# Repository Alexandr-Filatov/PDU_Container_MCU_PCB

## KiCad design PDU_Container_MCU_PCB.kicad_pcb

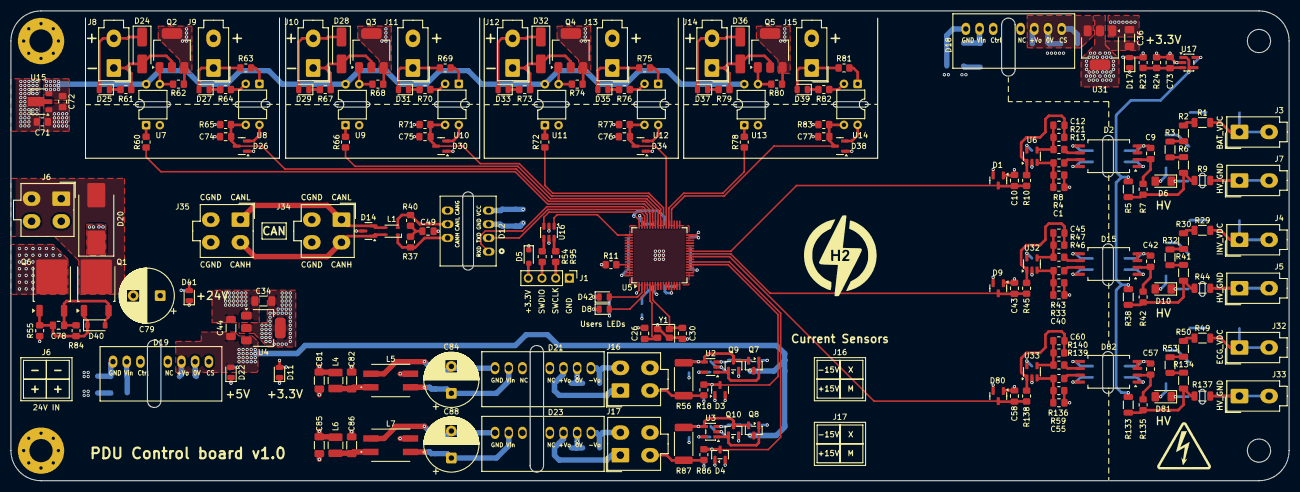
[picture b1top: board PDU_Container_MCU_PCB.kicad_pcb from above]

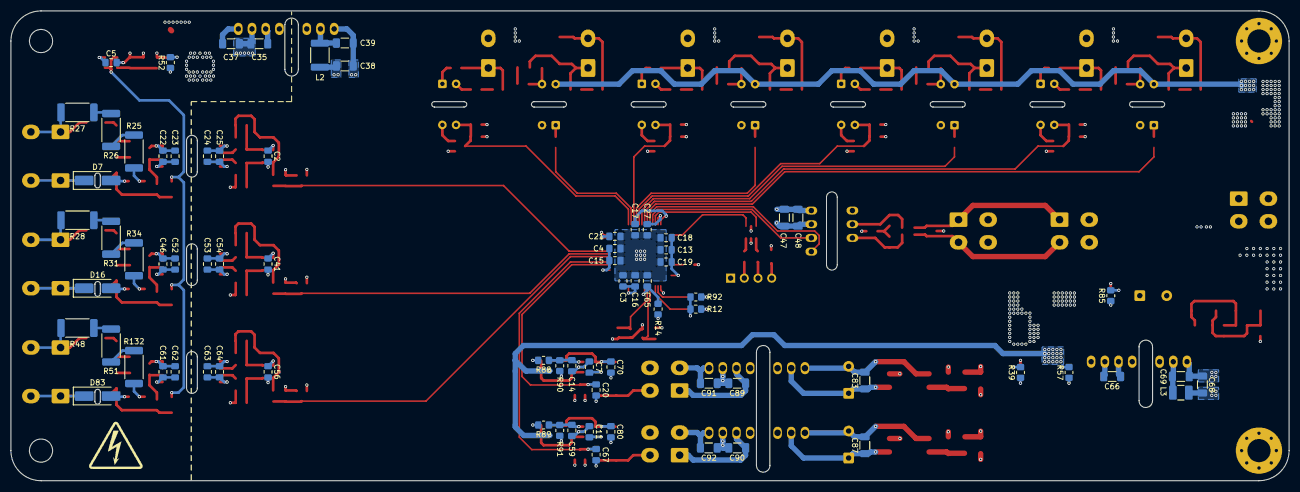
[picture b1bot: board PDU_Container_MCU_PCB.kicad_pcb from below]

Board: 4 copper layers, 237.2 x 87.2 mm, 283 parts (75 on the bottom side), 150 nets.

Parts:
C1, C9, C12, C40, C42, C45, C55, C57, C60: 56p; C_0805_2012Metric_Pad1.18x1.45mm_HandSolder
C2, C3, C4, C5, C7, C11, C13, C14, C15, C17, C18, C23, C25, C41, C52, C54, C56, C59, C62, C64, C65, C73, C78: 100n; C_0805_2012Metric_Pad1.18x1.45mm_HandSolder
C10, C43, C58: 220n; C_0805_2012Metric_Pad1.18x1.45mm_HandSolder
C16: 4.7u; C_0805_2012Metric_Pad1.18x1.45mm_HandSolder
C19, C74, C75, C76, C77: 1u; C_0805_2012Metric_Pad1.18x1.45mm_HandSolder
C20, C49, C67: 10n; C_0805_2012Metric_Pad1.18x1.45mm_HandSolder
C21, C22, C24, C27, C46, C53, C61, C63: 2.2u; C_0805_2012Metric_Pad1.18x1.45mm_HandSolder
C26, C30: 12p; C_0805_2012Metric_Pad1.18x1.45mm_HandSolder
C34, C35, C36, C37, C38, C44, C47, C66, C81, C82, C83, C85, C86, C87, C89, C90, C91, C92: 10u; C_1206_3216Metric_Pad1.33x1.80mm_HandSolder
C39: 1u; C_1206_3216Metric_Pad1.33x1.80mm_HandSolder
C48: 100n; C_1206_3216Metric_Pad1.33x1.80mm_HandSolder
C68, C69: 4.7u; C_1206_3216Metric_Pad1.33x1.80mm_HandSolder
C70, C71, C72, C80: 10u; C_0805_2012Metric_Pad1.18x1.45mm_HandSolder
C79, C84, C88: 330u; CP_Radial_D10.0mm_P5.00mm
D1, D3, D4, D9, D14, D26, D30, D34, D38, D80: SOT-23
D2, D15, D82: SOIC-8_7.5x5.85mm_P1.27mm
D5: D_SOD-323_HandSoldering
D6, D10, D81: LED_1206_3216Metric_Pad1.42x1.75mm_HandSolder
D7, D16, D24, D28, D32, D36, D83: D_SMA_Handsoldering
D8, D11, D17, D22, D25, D27, D29, D31, D33, D35, D37, D39, D41, D42: LED_0805_2012Metric
D12: TD5(3)01MCANFD
D13: Logo; Logo_Company_1
D18, D19: WRB_S-3WR2
D20: D_SMC_Handsoldering
D21, D23: UWE_S-3WR3
D40: D_SOD-123
H1, H2: MountingHole_Pad; MountingHole_4.3mm_M4_Pad_Via
H3, H4: MountingHole; MountingHole_4.3mm_M4
J1: PinHeader_1x04_P2.54mm_Vertical
J3, J4, J5, J7, J8, J9, J10, J11, J12, J13, J14, J15, J32, J33: Mini-Fit_01x02_Vertical
J6, J16, J17, J34, J35: Molex_Mini-Fit_Jr_5566-04A_2x02_P4.20mm_Vertical
L1: L_CommonModeChoke_TDK_ACM2520-2P
L2: 4.7u; L_1812_4532Metric_Pad1.30x3.40mm_HandSolder
L3: 6.8u; L_1210_3225Metric_Pad1.42x2.65mm_HandSolder
L4, L6: 4.7u; L_1210_3225Metric_Pad1.42x2.65mm_HandSolder
L5, L7: 470u; B82790S0513N201
Q1, Q6: TO-252-2
Q2, Q3, Q4, Q5: SOT-223
Q7, Q8, Q9, Q10: SOT-23
R1, R2, R3, R6, R29, R30, R32, R41, R49, R50, R53, R134: 2M; R_1206_3216Metric
R4, R8, R12, R13, R18, R21, R33, R39, R43, R46, R47, R52, R57, R59, R86, R92, R136, R139, R140: 1k; R_0805_2012Metric_Pad1.20x1.40mm_HandSolder
R5, R9, R38, R44, R133, R137: 8k; R_1206_3216Metric
R7, R10, R42, R45, R135, R138: 120; R_0805_2012Metric_Pad1.20x1.40mm_HandSolder
R11, R14, R24, R62, R65, R68, R71, R74, R77, R80, R83, R88, R89, R90, R91: 10k; R_0805_2012Metric_Pad1.20x1.40mm_HandSolder
R23: 23.2k; R_0805_2012Metric_Pad1.20x1.40mm_HandSolder
R25, R26, R27, R28, R31, R34, R48, R51, R132: 150k; R_2512_6332Metric_Pad1.40x3.35mm_HandSolder
R37, R40: 59; R_0805_2012Metric_Pad1.20x1.40mm_HandSolder
R54, R95: 20; R_0805_2012Metric_Pad1.20x1.40mm_HandSolder
R55: 100k; R_0805_2012Metric_Pad1.20x1.40mm_HandSolder
R56, R87: 14.3; R_2512_6332Metric_Pad1.40x3.35mm_HandSolder
R60, R66, R72, R78: 330; R_0805_2012Metric_Pad1.20x1.40mm_HandSolder
R61, R64, R67, R70, R73, R76, R79, R82: 8.2k; R_0805_2012Metric_Pad1.20x1.40mm_HandSolder
R63, R69, R75, R81: 3.3k; R_0805_2012Metric_Pad1.20x1.40mm_HandSolder
R84: 470k; R_0805_2012Metric_Pad1.20x1.40mm_HandSolder
R85: 4.7k; R_0805_2012Metric_Pad1.20x1.40mm_HandSolder
U2, U3, U6, U17, U32, U33: SOT-23-5
U4, U31: SOT-223-3_TabPin2
U5: LQFP-64_10x10mm_P0.5mm
U7, U8, U9, U10, U11, U12, U13, U14: DIP-4_W7.62mm
U15: SOT-89-3
U16: SOT-23-6
Y1: 16M; Crystal_SMD_SeikoEpson_FA238-4Pin_3.2x2.5mm

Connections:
+1V0: R5.2, R38.2, R133.2, U17.1, U17.4 (-)
+3.3V: C2.1, C3.1, C4.1, C7.1, C11.1, C13.1, C15.1, C16.1, C17.1, C18.1, C19.1, C24.2, C25.1, C34.2, C41.1, C47.1, C48.1, C53.2, C54.1, C56.1, C63.2, C64.1, D1.2 (K), D2.8 (VDD2), D3.2 (K), D4.2 (K), D5.1 (K), D9.2 (K), D11.2 (A), D12.4 (VCC), D15.8 (VDD2), D26.2 (K), D30.2 (K), D34.2 (K), D38.2 (K), D80.2 (K), D82.8 (VDD2), R14.1, R88.1, R89.1, U2.5 (V+), U3.5 (V+), U4.2 (VO), U5.1 (VBAT), U5.13 (VDDA), U5.19 (VDD), U5.32 (VDD), U5.48 (VDD), U5.64 (VDD), U6.5 (V+), U8.4, U10.4, U12.4, U14.4, U16.5 (VBUS), U32.5 (V+), U33.5 (V+)
+3.3VP: C5.1, C22.2, C23.1, C36.2, C46.2, C52.1, C61.2, C62.1, D2.1 (VDD1), D15.1 (VDD1), D17.2 (A), D82.1 (VDD1), R23.1, U17.5 (V+), U31.2 (VO)
+5V: C44.2, C66.1, D19.6 (+Vo), D22.2 (A), Q7.3 (C), Q8.3 (C), U4.3 (VI)
+5VD: C72.1, U7.4, U9.4, U11.4, U13.4, U15.3 (VOUT)
+24V: C38.1, C68.1, C71.1, C79.1, C81.1, C85.1, D20.1 (A1), D24.1 (K), D25.2 (A), D28.1 (K), D29.2 (A), D32.1 (K), D33.2 (A), D36.1 (K), D37.2 (A), D41.2 (A), J6.2, J6.4, J8.2, J9.2, J10.2, J11.2, J12.2, J13.2, J14.2, J15.2, L2.1, L3.1, L4.1, L6.1, R55.2, U15.2 (VIN)
-24V_IN: D20.2 (A2), J6.1, J6.3, Q1.2 (D)
/CANH: D14.1 (K), J34.2, J35.2, L1.4
/CANL: D14.2 (K), J34.1, J35.1, L1.3
/CAN_RXD_MCU: D12.1 (RXD), U5.44 (PA11)
/CAN_TXD_MCU: D12.2 (TXD), U5.45 (PA12)
/Current_1_measure: C20.1, D3.3 (common), R18.2, U5.21 (PA5)
/Current_2_measure: C67.1, D4.3 (common), R86.2, U5.22 (PA6)
/Current_measure_1/+15V: C89.1, D21.6 (+Vo), J16.1
/Current_measure_1/-15V: C91.2, D21.8 (-Vo), J16.2
/Current_measure_1/M: J16.3, R18.1, R56.2
/Current_measure_2/+15V: C90.1, D23.6 (+Vo), J17.1
/Current_measure_2/-15V: C92.2, D23.8 (-Vo), J17.2
/Current_measure_2/M: J17.3, R86.1, R87.2
/Relay_Control_1: R60.1, U5.43 (PA10)
/Relay_Control_2: R66.1, U5.41 (PA8)
/Relay_Control_3: R72.1, U5.39 (PC8)
/Relay_Control_4: R78.1, U5.37 (PC6)
/Relay_FeedBack_1: C74.1, D26.3 (common), R65.1, U5.42 (PA9), U8.3
/Relay_FeedBack_2: C75.1, D30.3 (common), R71.1, U5.40 (PC9), U10.3
/Relay_FeedBack_3: C76.1, D34.3 (common), R77.1, U5.38 (PC7), U12.3
/Relay_FeedBack_4: C77.1, D38.3 (common), R83.1, U5.36 (PB15), U14.3
/SWCLK: U5.49 (PA14), U16.1 (I/O1)
/SWDIO: U5.46 (PA13), U16.3 (I/O2)
/VDC_1_measure: C10.1, D1.3 (common), R10.2, U5.26 (PB0)
/VDC_2_measure: C43.1, D9.3 (common), R45.2, U5.25 (PC5)
/VDC_3_measure: C58.1, D80.3 (common), R138.2, U5.24 (PC4)
BOOT0: R11.2, U5.60 (BOOT0)
GND: C1.1, C2.2, C3.2, C4.2, C7.2, C10.2, C11.2, C13.2, C14.1, C15.2, C16.2, C17.2, C18.2, C19.2, C20.2, C21.2, C24.1, C25.2, C26.1, C27.2, C30.2, C34.1, C40.1, C41.2, C43.2, C44.1, C47.2, C48.2, C53.1, C54.2, C55.1, C56.2, C58.2, C59.1, C63.1, C64.2, C65.1, C66.2, C67.2, C70.2, C74.2, C75.2, C76.2, C77.2, C80.2, C89.2, C90.2, C91.1, C92.1, D1.1 (A), D2.5 (GND2), D3.1 (A), D4.1 (A), D9.1 (A), D12.3 (GND), D15.5 (GND2), D19.7 (0V), D21.7 (0V), D23.7 (0V), D26.1 (A), D30.1 (A), D34.1 (A), D38.1 (A), D80.1 (A), D82.5 (GND2), J1.1, Q9.2 (E), Q10.2 (E), R4.1, R11.1, R12.2, R33.1, R39.2, R57.2, R59.1, R65.2, R71.2, R77.2, R83.2, R90.1, R91.1, R92.2, U2.2 (V-), U3.2 (V-), U4.1 (GND), U5.12 (VSSA), U5.18 (VSS), U5.63 (VSS), U6.2 (V-), U7.2, U9.2, U11.2, U13.2, U16.2 (GND), U32.2 (V-), U33.2 (V-), Y1.2, Y1.4
GNDD: C38.2, C39.2, C68.2, C69.2, C71.2, C72.2, C79.2, C81.2, C82.2, C85.2, C86.2, D18.1 (GND), D19.1 (GND), H1.1 (1_1), H2.1 (1_1), L5.3, L7.3, Q2.3 (S), Q2.4 (S), Q3.3 (S), Q3.4 (S), Q4.3 (S), Q4.4 (S), Q5.3 (S), Q5.4 (S), Q6.2 (D), R62.1, R64.2, R68.1, R70.2, R74.1, R76.2, R80.1, R82.2, R85.2, U8.2, U10.2, U12.2, U14.2, U15.1 (GND)
GNDPWR: C5.2, C9.2, C22.1, C23.2, C35.1, C36.1, C37.1, C42.2, C46.1, C52.2, C57.2, C61.1, C62.2, C73.1, D2.3 (SHTDN), D2.4 (GND1), D7.1 (K), D15.3 (SHTDN), D15.4 (GND1), D16.1 (K), D18.7 (0V), D82.3 (SHTDN), D82.4 (GND1), D83.1 (K), J5.1, J5.2, J7.1, J7.2, J33.1, J33.2, R9.1, R24.2, R44.1, R52.2, R137.1, U17.2 (V-), U31.1 (GND)
GND_CAN: C49.2, D12.5 (CANG), D14.3 (A), J34.3, J34.4, J35.3, J35.4
NRST: C65.2, R14.2, U5.7 (NRST)
unnamed: C12.2, R10.1, R21.2, U6.1
unnamed: C45.2, R45.1, R47.2, U32.1
unnamed: C49.1, R37.1, R40.2
unnamed: C60.2, R138.1, R140.2, U33.1
unnamed: C82.1, L4.2, L5.1
unnamed: C86.1, L6.2, L7.1
unnamed: D2.6 (OUTN), R13.1
unnamed: D2.7 (OUTP), R8.1
unnamed: C9.1, D2.2 (VIN), R7.1
unnamed: D5.2 (A), J1.4
unnamed: D6.2 (A), R25.2
unnamed: D6.1 (K), D7.2 (A)
unnamed: D8.2 (A), U5.3 (PC14)
unnamed: D8.1 (K), R12.1
unnamed: D10.2 (A), R34.2
unnamed: D10.1 (K), D16.2 (A)
unnamed: D11.1 (K), R39.1
unnamed: D12.7 (CANH), L1.1, R37.2
unnamed: D12.6 (CANL), L1.2, R40.1
unnamed: D15.6 (OUTN), R46.1
unnamed: D15.7 (OUTP), R43.1
unnamed: C42.1, D15.2 (VIN), R42.1
unnamed: D17.1 (K), R52.1
unnamed: C35.2, D18.6 (+Vo), U31.3 (VI)
unnamed: C37.2, D18.8 (CS)
unnamed: C39.1, D18.2 (Vin), L2.2
unnamed: C69.1, D19.2 (Vin), L3.2
unnamed: C83.2, C84.2, D21.1 (GND), L5.4
unnamed: C83.1, C84.1, D21.2 (Vin), L5.2
unnamed: D22.1 (K), R57.1
unnamed: C87.2, C88.2, D23.1 (GND), L7.4
unnamed: C87.1, C88.1, D23.2 (Vin), L7.2
unnamed: D24.2 (A), J8.1, Q2.2 (D), R61.2
unnamed: D25.1 (K), R61.1
unnamed: D27.2 (A), J9.1, R63.2
unnamed: D27.1 (K), R64.1
unnamed: D28.2 (A), J10.1, Q3.2 (D), R67.2
unnamed: D29.1 (K), R67.1
unnamed: D31.2 (A), J11.1, R69.2
unnamed: D31.1 (K), R70.1
unnamed: D32.2 (A), J12.1, Q4.2 (D), R73.2
unnamed: D33.1 (K), R73.1
unnamed: D35.2 (A), J13.1, R75.2
unnamed: D35.1 (K), R76.1
unnamed: D36.2 (A), J14.1, Q5.2 (D), R79.2
unnamed: D37.1 (K), R79.1
unnamed: D39.2 (A), J15.1, R81.2
unnamed: D39.1 (K), R82.1
unnamed: C78.2, D40.2 (A), Q1.3 (S), Q6.3 (S), R84.2
unnamed: C78.1, D40.1 (K), Q1.1 (G), Q6.1 (G), R55.1, R84.1
unnamed: D41.1 (K), R85.1
unnamed: D42.2 (A), U5.2 (PC13)
unnamed: D42.1 (K), R92.1
unnamed: D81.2 (A), R132.2
unnamed: D81.1 (K), D83.2 (A)
unnamed: D82.6 (OUTN), R139.1
unnamed: D82.7 (OUTP), R136.1
unnamed: C57.1, D82.2 (VIN), R135.1
unnamed: J1.2, R95.2
unnamed: J1.3, R54.2
unnamed: J3.1, J3.2, R1.2, R27.1
unnamed: J4.1, J4.2, R28.1, R29.2
unnamed: J32.1, J32.2, R48.1, R49.2
unnamed: Q2.1 (G), R62.2, U7.3
unnamed: Q3.1 (G), R68.2, U9.3
unnamed: Q4.1 (G), R74.2, U11.3
unnamed: Q5.1 (G), R80.2, U13.3
unnamed: Q7.1 (B), Q9.1 (B), U2.1
unnamed: C70.1, Q7.2 (E), Q9.3 (C), R56.1, U2.4 (-)
unnamed: Q8.1 (B), Q10.1 (B), U3.1
unnamed: C80.1, Q8.2 (E), Q10.3 (C), R87.1, U3.4 (-)
unnamed: R1.1, R2.2
unnamed: R2.1, R3.2
unnamed: R3.1, R6.2
unnamed: R5.1, R6.1, R7.2, R9.2
unnamed: R25.1, R26.2
unnamed: R26.1, R27.2
unnamed: R28.2, R31.1
unnamed: R29.1, R30.2
unnamed: R30.1, R32.2
unnamed: R31.2, R34.1
unnamed: R32.1, R41.2
unnamed: R38.1, R41.1, R42.2, R44.2
unnamed: R48.2, R51.1
unnamed: R49.1, R50.2
unnamed: R50.1, R53.2
unnamed: R54.1, U16.4 (I/O2)
unnamed: R60.2, U7.1
unnamed: R63.1, U8.1
unnamed: R66.2, U9.1
unnamed: R69.1, U10.1
unnamed: R72.2, U11.1
unnamed: R75.1, U12.1
unnamed: R78.2, U13.1
unnamed: R81.1, U14.1
unnamed: R95.1, U16.6 (I/O1)
unnamed: R51.2, R132.1
unnamed: R133.1, R134.1, R135.2, R137.2
unnamed: R53.1, R134.2
unnamed: C14.2, R88.2, R90.2, U2.3 (+)
unnamed: C59.2, R89.2, R91.2, U3.3 (+)
unnamed: C26.2, U5.5 (PH0), Y1.3
unnamed: C30.1, U5.6 (PH1), Y1.1
unnamed: C21.1, U5.31 (VCAP_1)
unnamed: C27.1, U5.47 (VCAP_2)
unnamed: C1.2, R4.2, R8.2, U6.3 (+)
unnamed: C12.1, R13.2, R21.1, U6.4 (-)
unnamed: C73.2, R23.2, R24.1, U17.3 (+)
unnamed: C40.2, R33.2, R43.2, U32.3 (+)
unnamed: C45.1, R46.2, R47.1, U32.4 (-)
unnamed: C55.2, R59.2, R136.2, U33.3 (+)
unnamed: C60.1, R139.2, R140.1, U33.4 (-)

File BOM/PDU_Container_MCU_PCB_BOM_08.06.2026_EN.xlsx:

Reference | Value | Product Name | Replacement | Package | Description | Quantity | DNP
C23, C25, C52, C54, C62, C64 | 0.1u |  |  | SMD 0805 |  | 6
C48 | 0.1u |  |  | SMD 1206 |  | 1
C10, C43, C58 | 0.27u |  |  | SMD 0805 |  | 3
C2, C3, C5, C7, C11, C14, C16, C17, C18, C19, C27, C28, C29, C32, C33, C41, C56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 | 100n |  |  | SMD 0805 |  | 19
C78 | 100n |  |  | SMD 0805 | Capacitor SMD 50V | 1
C20, C49, C67 | 10n |  |  | SMD 0805 |  | 3
C70, C71, C72, C80 | 10u |  |  | SMD 0805 |  | 4
C34, C35, C36, C37, C38, C44, C47 | 10u |  |  | SMD 1206 |  | 7
C66, C81, C82, C83, C85, C86, C87, C89, C90, C91, C92 | 10u |  |  | SMD 1206 | Capacitor SMD 50V | 11
C26, C30 | 12p |  |  | SMD 0805 |  | 2
C4, C6, C74, C75, C76, C77 | 1u |  |  | SMD 0805 |  | 6
C39 | 1u |  |  | SMD 1206 |  | 1
C22, C24, C46, C50, C51, C53, C61, C63 | 2.2u |  |  | SMD 0805 |  | 8
C79, C84, C88 | 330u | EEUFR1H331L |  | CP Radial D10.0mm P5.00mm | Polarized capacitor | 3
C31 | 4.7u |  |  | SMD 0805 |  | 1
C68, C69 | 4.7u |  |  | SMD 1206 | Capacitor SMD 50V | 2
C1, C9, C12, C40, C42, C45, C55, C57, C60 | 56p |  |  | SMD 0805 |  | 9
D7, D16, D83 | S1M |  |  | SMA |  | 3
D12 | TD301MCANFD |  |  | TD5(3)01MCANFD |  | 1
D6, D10, D81 | TO-3216BC-MYF |  |  | SMD 1206 |  | 3
D24, D28, D32, D36 | ~ | RS1B |  | SMA | Fast recovery diode | 4
D20 | ~ | SMCJ33A |  | SMC | Supressor | 1
D8, D13, D25, D29, D33, D37 | ~ | FYLS-0805UBC |  | SMD 0805 | Blue LED | 6
D11, D17, D22, D27, D31, D35, D39, D41 | ~ | FYLS-0805UYC |  | SMD 0805 | Yellow LED | 8
D40 | ~ | BZT52C10 |  | SOD-123 | Zener_Diode | 1
D5 | ~ | BAS416 |  | SOD-323 | Diode | 1
D2, D15, D82 | ~ | NSI1311 |  | SOIC-8 7.5x5.85mm P1.27mm | Isolated amplifier | 3
D14 | ~ | SM24CANB-02HTG |  | SOT-23 | Dual Line CAN Bus Protector, 24Vrwm | 1
D1, D3, D4, D9, D26, D30, D34, D38, D80 | ~ | BAT54S |  | SOT-23 | Schottky barrier diode | 9
D21, D23 | ~ |  |  | UWE S-3WR3 |  | 2
D18 | ~ | WRB2403S-3WR2 |  | WRB S-3WR2 | DC/DC converter | 1
D19 | ~ | WRB2405S-3WR2 |  | WRB S-3WR2 | DC/DC | 1
F2 | ~ | MF-MSMF050/30X-2 |  | SMD 1812 | Fuse SMD | 1
J3, J4, J5, J7, J8, J9, J10, J11, J12, J13, J14, J15, J32, J33 | ~ | DS1073-01-2x1-MVT6 |  | Mini-Fit 01x02 | Connector | 14
J2, J34 | ~ | DS1073-01-2x2-MVT6 |  | Molex Mini-Fit Jr 5566-04A 2x02 P4.20mm | Connector | 2
J6, J16, J17 | ~ | DS1073-01-2x2MR3T6 |  | Molex Mini-Fit Jr 5566-04A 2x02 P4.20mm | Connector | 3
J1 | ~ | PLS-4 | DS-1021-1x4 | PinHeader 1x04 P2.54mm | Connector | 1
L4, L6 | 4.7u | LQH44PN4R7MP0L |  | SMD 1210 | Inductor SMD | 2
L2 | 4.7u | NLC453232T-4R7K-PF |  | SMD 1812 |  | 1
L5, L7 | 470u | B82790C0474N215 |  | B82790S0513N201 |  | 2
L3 | 6.8u | LQH32CN6R8M53L |  | SMD 1210 | Inductor SMD | 1
L1 | ~ |  |  | CommonModeChoke TDK ACM2520-2P |  | 1
Q7, Q8 | BC847 |  |  | SOT-23 |  | 2
Q9, Q10 | BC857 |  |  | SOT-23 |  | 2
Q2, Q3, Q4, Q5 | ~ | BSP75N |  | SOT-223 | Self-Protected Low Side Driver with Temperature and Current Limit, SOT−223 | 4
Q1, Q6 | ~ | 20N06 |  | TO-252-2 | N_channel MOSFET | 2
R57 | 1.1k |  |  | SMD 0805 | Resistor SMD | 1
R55 | 100k |  |  | SMD 0805 | Resistor SMD | 1
R62, R65, R68, R71, R74, R77, R80, R83, R88, R89, R90, R91 | 10k |  |  | SMD 0805 |  | 12
R7, R42, R135 | 120 |  |  | SMD 0805 |  | 3
R56, R87 | 14.3 |  |  | SMD 0805 |  | 2
R25, R26, R27, R28, R31, R34, R48, R51, R132 | 150k |  |  | SMD 1206 |  | 9
R5, R9, R38, R44, R133, R137 | 16k |  |  | SMD 1206 |  | 6
R4, R8, R13, R16, R17, R18, R21, R24, R33, R35, R36, R43, R46, R47, R58, R59, R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 | 1k |  |  | SMD 0805 |  | 20
R23 | 240 |  |  | SMD 0805 |  | 1
R1, R2, R3, R6, R29, R30, R32, R41, R49, R50, R53, R134 | 2M |  |  | SMD 1206 |  | 12
R63, R69, R75, R81 | 3.3k |  |  | SMD 0805 |  | 4
R60, R66, R72, R78 | 330 |  |  | SMD 0805 |  | 4
R85 | 4.7k |  |  | SMD 0805 | Resistor SMD | 1
R84 | 470k |  |  | SMD 0805 | Resistor SMD | 1
R10, R45, R138 | 49.9 |  |  | SMD 0805 |  | 3
R37, R40 | 59 |  |  | SMD 0805 |  | 2
R39, R52 | 750 |  |  | SMD 0805 |  | 2
R61, R64, R67, R70, R73, R76, R79, R82 | 8.2k |  |  | SMD 0805 |  | 8
U15 | HT75xx-1-SOT89 | HT7550-1 |  | SOT-89-3 |  | 1
U2, U3, U6, U32, U33 | OPA333xxDBV |  |  | SOT-23-5 |  | 5
U7, U8, U9, U10, U11, U12, U13, U14 | PC817 |  |  | DIP-4 W7.62mm |  | 8
U4, U31 | TLV1117LV33DCYR |  |  | SOT-223-3 |  | 2
U1 | TLV431 |  |  | SOT-23 |  | 1
U5 | ~ | APM32F405xG |  | LQFP-100 14x14mm P0.5mm | uController | 1
Y1 | ~ | X322516MOB4SI |  | Crystal SMD SeikoEpson FA238-4Pin 3.2x2.5mm | Crystal | 1

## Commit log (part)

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2026-06-05 zero commit
2026-06-08 VER1.0: добавил функционалку и расставил все на плате
2026-06-09 VER1.0: оптимизировал схему измерения напряжения
2026-06-10 VER1.0: плата разведена
2026-06-11 VER1.0: плата разведена, файлы по плате готовы
2026-06-11 VER1.0: поправил BOM
